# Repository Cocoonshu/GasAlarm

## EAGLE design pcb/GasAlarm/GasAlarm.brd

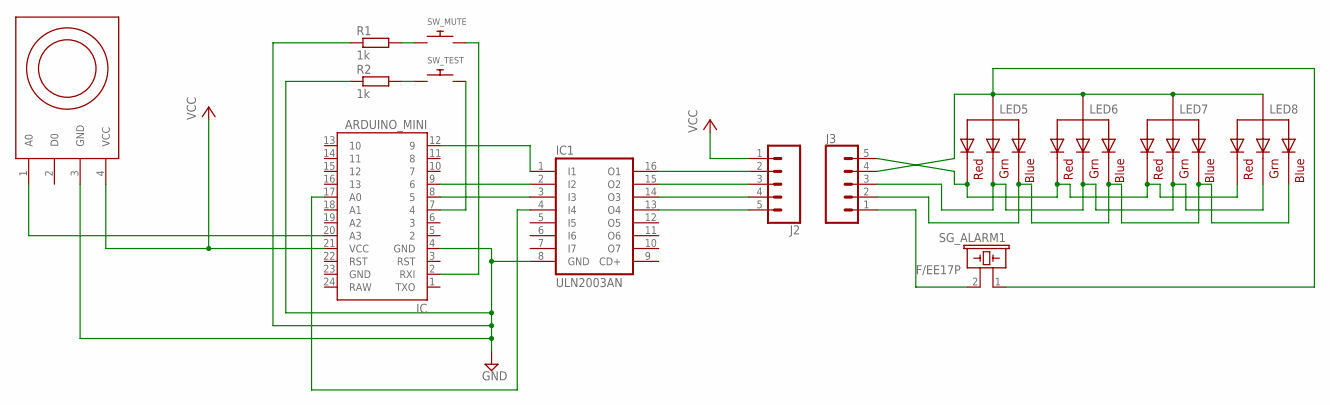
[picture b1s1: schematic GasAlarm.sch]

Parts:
IC: ARDUINO_MINI
IC1: ULN2003AN; DIL16
J2, J3: CONN_05; 1X05
LED5, LED6, LED7, LED8: RGBLED_CA-5MM; LED5MMRGB
MQ6: MQ-6; DIP4-MQ_6
R1, R2: 1k; 0204/5
SG_ALARM1: F/EE17P
SW_MUTE: SWITCH_PUSHBUTTONSOFTTOUCHSMD_SJ; PUSHBUTTON_SMD_SJ
SW_TEST: SWITCH_PUSHBUTTONSOFTTOUCHSMD_SJ; PUSHBUTTON_SMD_SJ

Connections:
GND: IC.4 (GND), IC1.8 (GND), MQ6.3 (GND), R1.1, R2.1
unnamed: IC1.16 (O1), J2.2
unnamed: IC1.15 (O2), J2.3
unnamed: IC1.14 (O3), J2.4
unnamed: IC1.13 (O4), J2.5
unnamed: IC.7 (4), SW_TEST.P$2
unnamed: IC.8 (5), IC1.3 (I3)
unnamed: IC.9 (6), IC1.2 (I2)
unnamed: IC.12 (9), IC1.1 (I1)
unnamed: IC.2 (RXI), SW_MUTE.P$2
unnamed: R2.2, SW_TEST.P$1
unnamed: R1.2, SW_MUTE.P$1
unnamed: IC.20 (A3), MQ6.1 (A0)
unnamed: IC.17 (A0), IC1.4 (I4)
unnamed: J3.5, LED5.1 (RED), LED6.1 (RED), LED7.1 (RED), LED8.1 (RED)
unnamed: J3.4, LED5.2 (VCC), LED6.2 (VCC), LED7.2 (VCC), LED8.2 (VCC), SG_ALARM1.1
unnamed: J3.3, LED5.3 (GREEN), LED6.3 (GREEN), LED7.3 (GREEN), LED8.3 (GREEN)
unnamed: J3.2, LED5.4 (BLUE), LED6.4 (BLUE), LED7.4 (BLUE), LED8.4 (BLUE)
unnamed: J3.1, SG_ALARM1.2
VCC: IC.21 (VCC), J2.1, MQ6.4 (VCC)

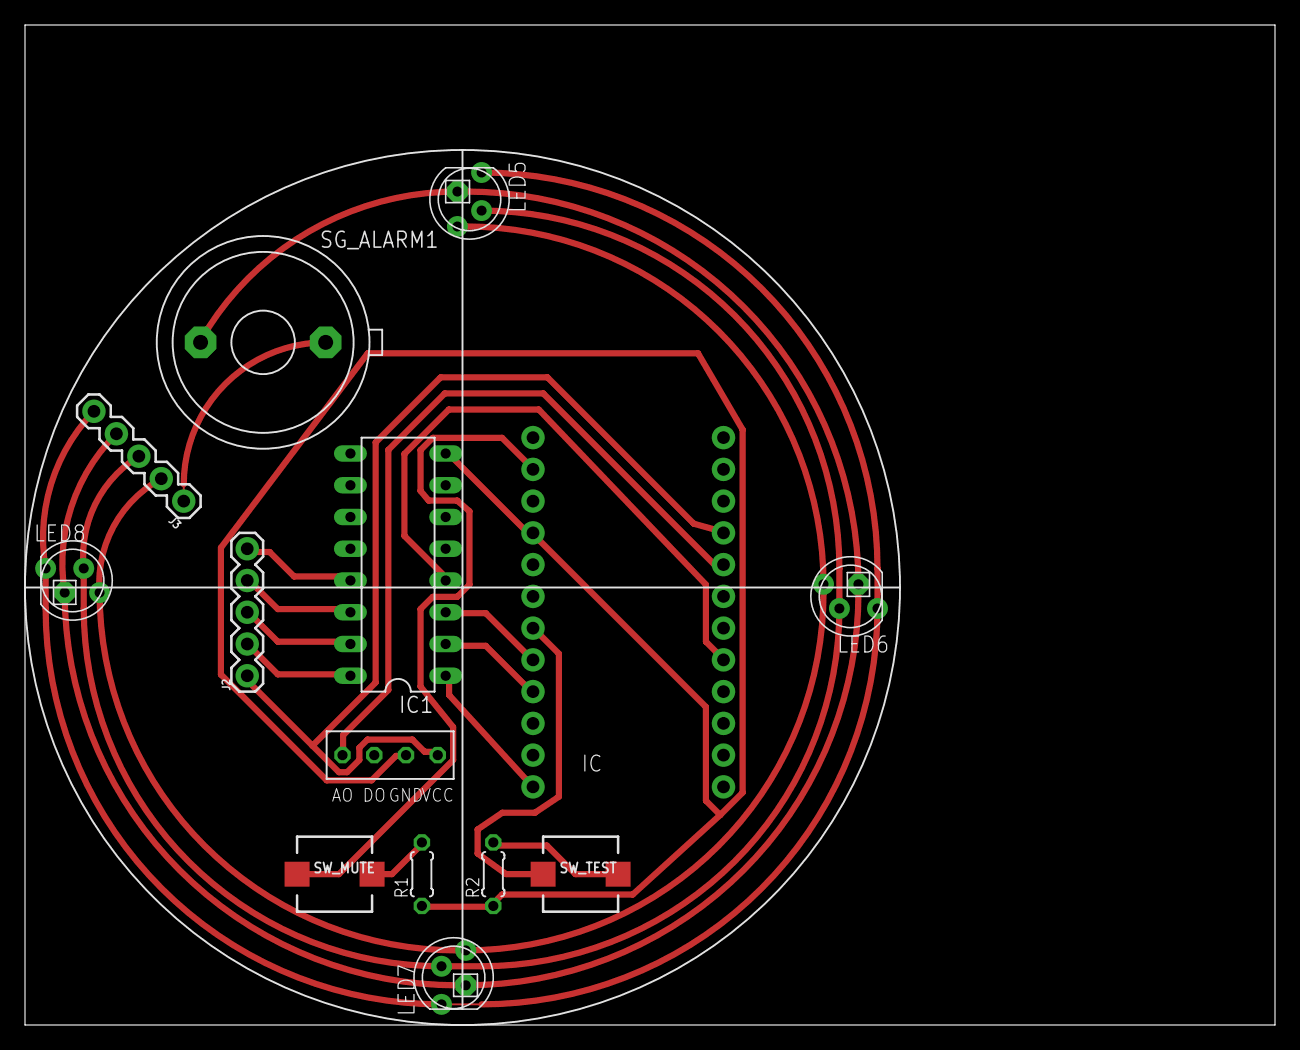
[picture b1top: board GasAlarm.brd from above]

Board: 2 copper layers, 100.0 x 80.0 mm, 14 parts (0 on the bottom side), 20 nets.

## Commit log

2017-11-23 init
2017-11-23 警报级别切换时，呼吸灯的呼吸能够平滑过渡
2017-11-25 增加电路工程
2017-11-26 更新电路
2017-11-29 pcb完成

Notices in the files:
parts and their libraries:
SparkFun-Retired: Licensing: Creative Commons ShareAlike 4.0 International - https://creativecommons.org/licenses/by-sa/4.0
